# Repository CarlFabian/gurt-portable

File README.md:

# gurt-portable
A wireless portable keyboard with a 34 key layout designed with simplicity in mind. 

## Inspiration
This keyboard was based of durken1's *[pierce](https://github.com/durken1/pierce)*. The building instructions and bill of materials is identical to the wireless version and uses the same dongle pcb. Just make sure to use the firmware from this repository or the keyboard will not work as expected. Big shoutout to durken1 for his amazing work and for the help I got to make this project possible.

# v0.2 (not tested but probably better)
**changes:**
<ul>
  <li>Slightly bigger solderpads for the battery holders as I had problems soldering the ones I ordered from Aliexpress.</li>
  <li>Thumbkeys has new footprints that allows the switches to be rotated 90°</li>
</ul>

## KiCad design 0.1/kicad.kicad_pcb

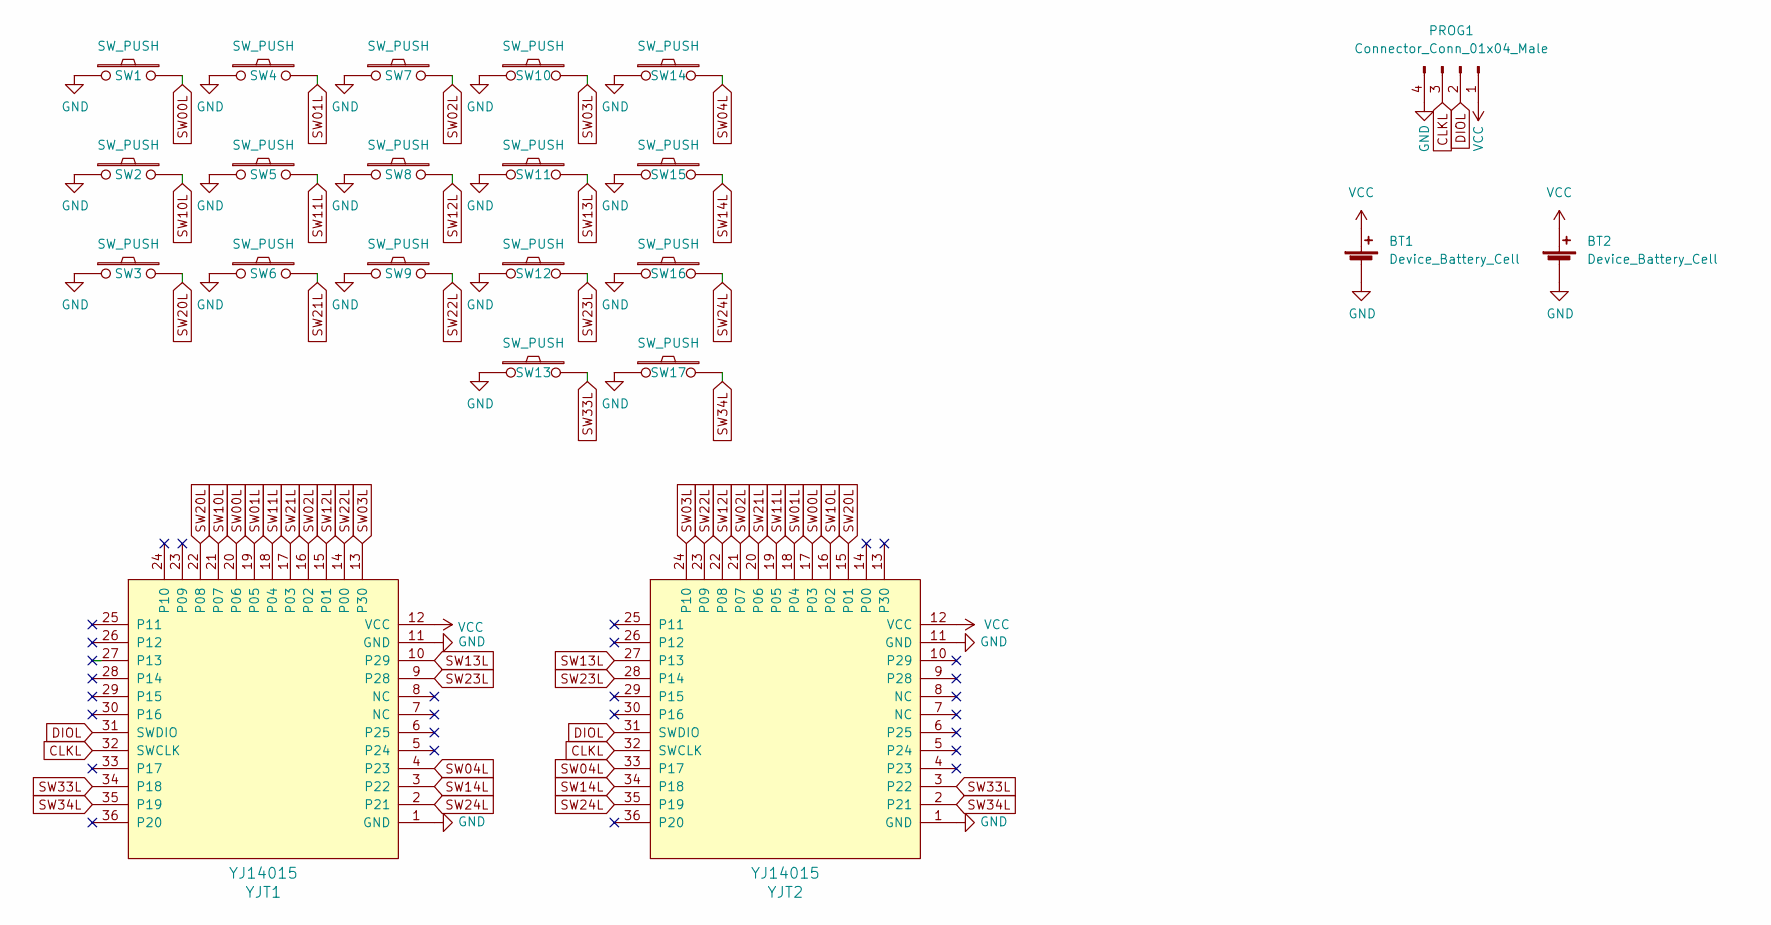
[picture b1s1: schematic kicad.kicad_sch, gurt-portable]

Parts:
BT1, BT2: Device_Battery_Cell; BatteryHolder_Keystone_3034_1x20mm
PROG1: Connector_Conn_01x04_Male; PinHeader_1x04_P2.54mm_Horizontal
SW1, SW2, SW3, SW4, SW5, SW6, SW7, SW8, SW9, SW10, SW11, SW12, SW13, SW14, SW15, SW16, SW17: SW_PUSH; Choc_PG1350_Choc_Spacing_Reversible
YJT1, YJT2: YJ14015; YJ-14015

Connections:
CLKL: PROG1.3, YJT1.32 (SWCLK), YJT2.32 (SWCLK)
DIOL: PROG1.2, YJT1.31 (SWDIO), YJT2.31 (SWDIO)
GND: BT1.2 (-), BT2.2 (-), PROG1.4, SW1.1, SW2.1, SW3.1, SW4.1, SW5.1, SW6.1, SW7.1, SW8.1, SW9.1, SW10.1, SW11.1, SW12.1, SW13.1, SW14.1, SW15.1, SW16.1, SW17.1, YJT1.1 (GND), YJT1.11 (GND), YJT2.1 (GND), YJT2.11 (GND)
SW00L: SW1.2, YJT1.20 (P06), YJT2.17 (P03)
SW01L: SW4.2, YJT1.19 (P05), YJT2.18 (P04)
SW02L: SW7.2, YJT1.16 (P02), YJT2.21 (P07)
SW03L: SW10.2, YJT1.13 (P30), YJT2.24 (P10)
SW04L: SW14.2, YJT1.4 (P23), YJT2.33 (P17)
SW10L: SW2.2, YJT1.21 (P07), YJT2.16 (P02)
SW11L: SW5.2, YJT1.18 (P04), YJT2.19 (P05)
SW12L: SW8.2, YJT1.15 (P01), YJT2.22 (P08)
SW13L: SW11.2, YJT1.10 (P29), YJT2.27 (P13)
SW14L: SW15.2, YJT1.3 (P22), YJT2.34 (P18)
SW20L: SW3.2, YJT1.22 (P08), YJT2.15 (P01)
SW21L: SW6.2, YJT1.17 (P03), YJT2.20 (P06)
SW22L: SW9.2, YJT1.14 (P00), YJT2.23 (P09)
SW23L: SW12.2, YJT1.9 (P28), YJT2.28 (P14)
SW24L: SW16.2, YJT1.2 (P21), YJT2.35 (P19)
SW33L: SW13.2, YJT1.34 (P18), YJT2.3 (P22)
SW34L: SW17.2, YJT1.35 (P19), YJT2.2 (P21)
VCC: BT1.1 (+), BT2.1 (+), PROG1.1, YJT1.12 (VCC), YJT2.12 (VCC)

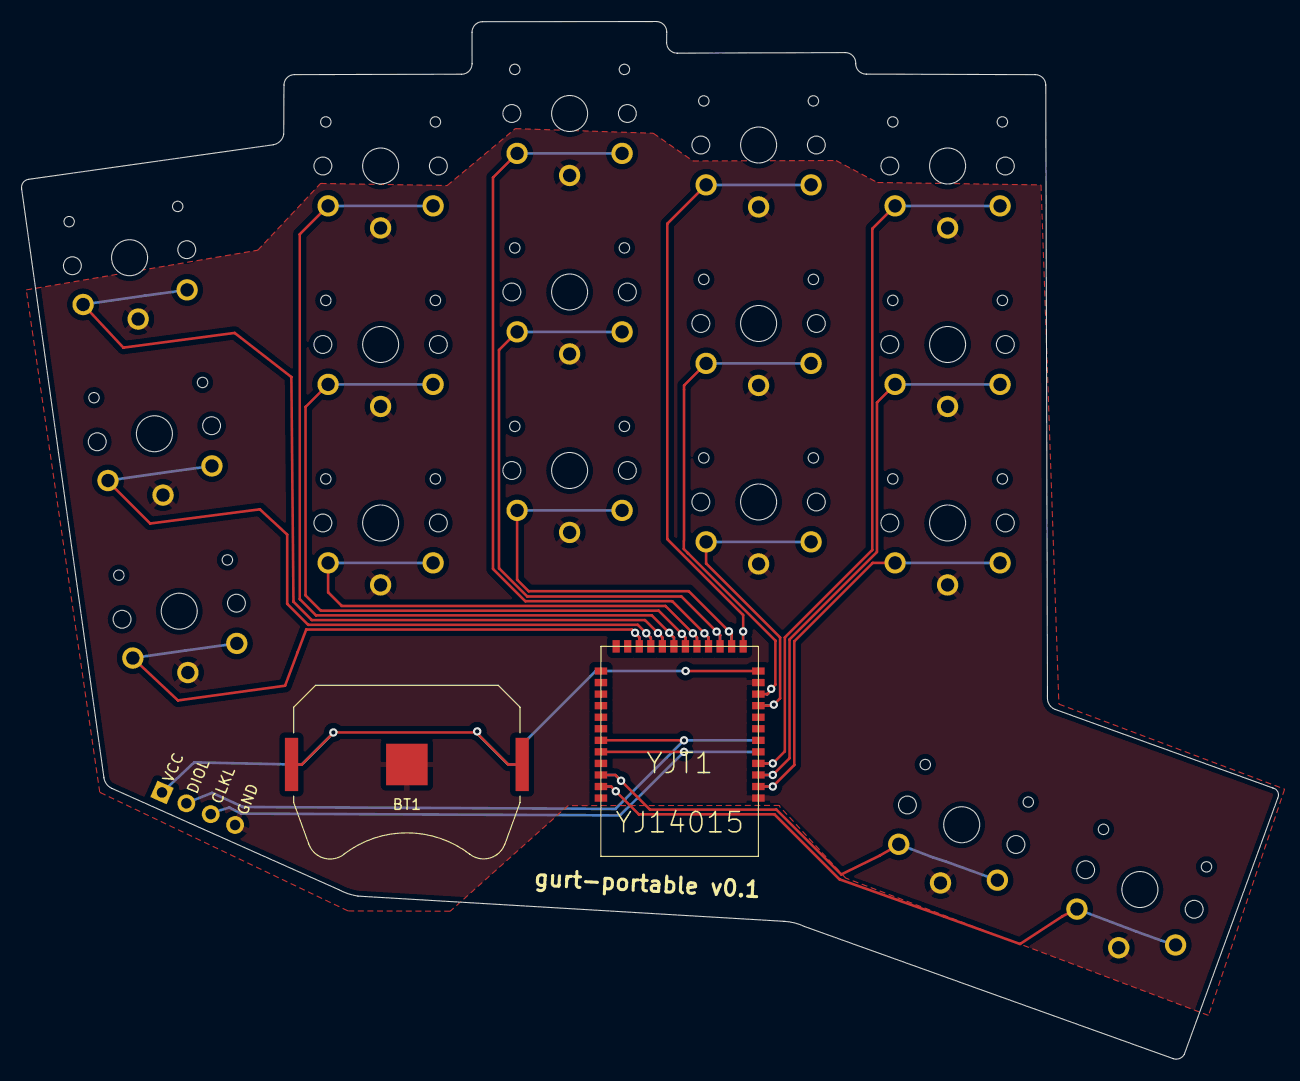
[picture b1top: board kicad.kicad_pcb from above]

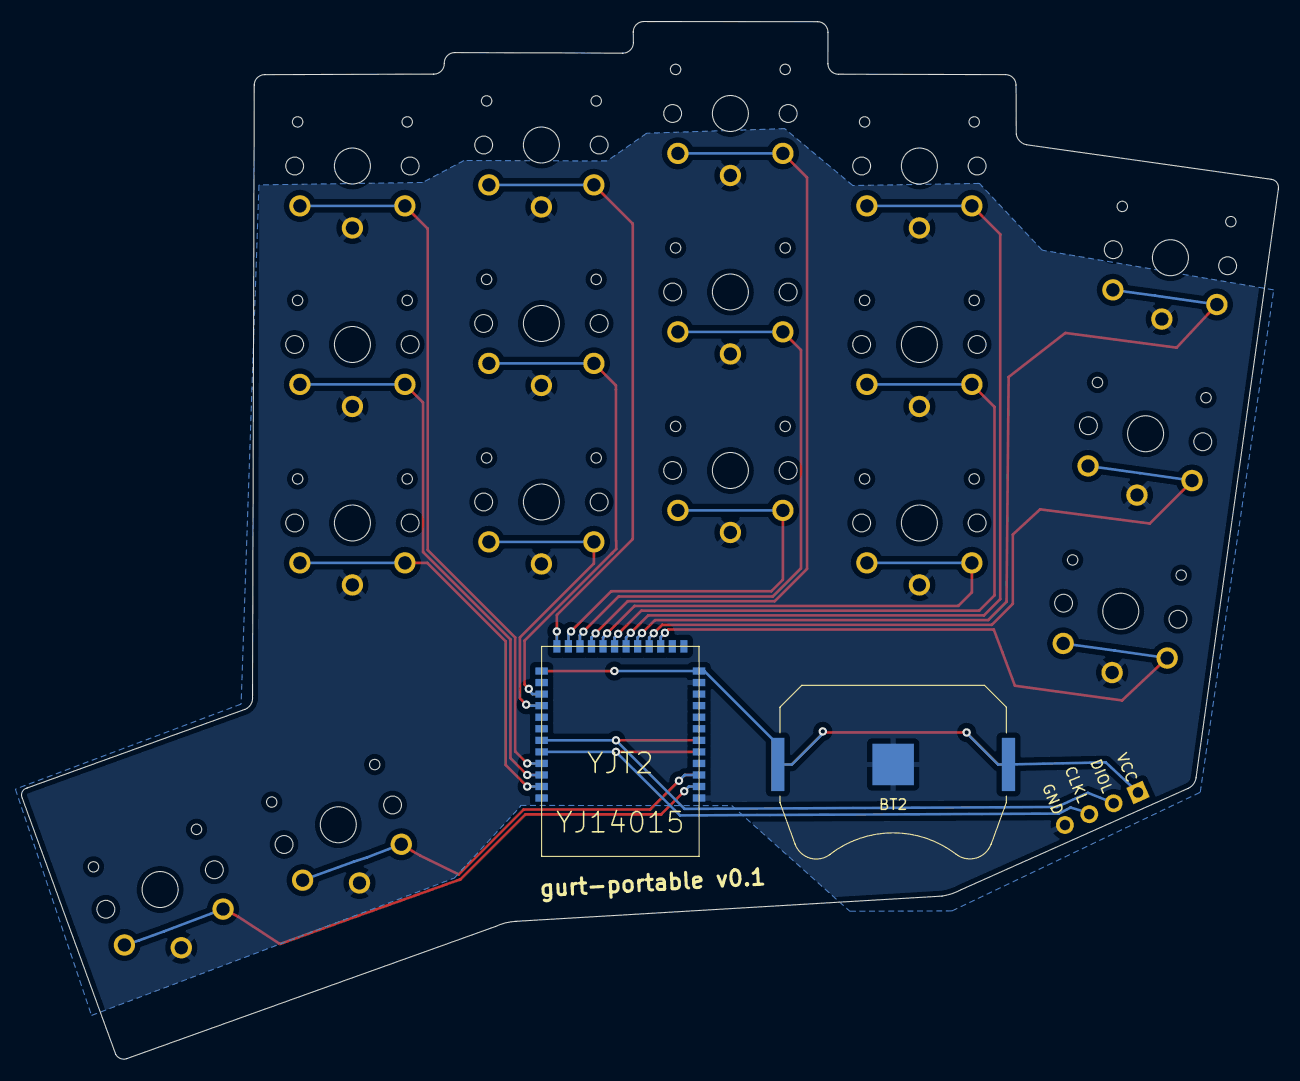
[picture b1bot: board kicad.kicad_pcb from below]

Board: 2 copper layers, 119.7 x 98.8 mm, 22 parts (3 on the bottom side), 21 nets.

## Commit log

2022-04-23 Update LICENSE
2022-04-23 added kicad files and started in schematic
2022-04-29 kicad stuff
2022-04-30 fixed schema and drew traces
2022-04-30 schema save
2022-05-01 Added outline and made it look nicer
2022-05-01 Updated shape
2022-05-01 Made things look nicer
2022-05-02 ordered pcbs
2022-05-03 fixed ordere
2022-05-24 added firmware files for wireless modules
2022-05-24 fixed
2022-07-13 Create helo
2022-07-13 Create hh
2022-07-13 Added 0.2
    The 0.2 version of the pcb has slightly bigger pads for the battery to make it easier to solder when using aliexpress battery holders. The thumb buttons also have a new footprint that makes it possib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
2022-07-13 added pictures
2022-07-13 Added dongle firmware
2022-07-15 removed silkscreentext
2022-07-15 update picture
2022-07-15 new picture and gerbers
2022-10-12 Changed shape of programmer pins
    changed the shape of the programmer pins so that the rectangle is for ground
2022-10-12 revert to working
2022-10-12 Revert "Update README.md"
    This reverts commit 14f0d408cb58860ee4602d8263bbf30b502f116b.
2022-10-12 fixed programmer pads
